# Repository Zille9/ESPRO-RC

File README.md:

# ESPRO-RC
Propeller-ESP32-Retro-Computer
- Der ESPRO-RC ist ein Minicomputer bestehend aus dem Parallax Propeller-IC (P8x32A) und einem ESP32 Dev-Kit als Grafik-Unit.
- Er kombiniert die einfache Programmierbarkeit und die Möglichkeit Programme von SD-Karte zu starten 
- mit den Grafikfähigkeiten der FabGl-Library im ESP32 als leistungsfähiges VGA-Terminal
- Als RAM wird ein PSRAM64H mit 8MByte Ram verwendet.
- Hauptprogramm ist ein umfangreicher Basic-Interpreter (weitere Programme sollen folgen)

Zur Installation werden benötigt:
- Arduino-IDE mit ESP32-Erweiterung
- FabGl-Library
- BST-Propeller-Compiler (im Ordner Software/P8X32A/BST)

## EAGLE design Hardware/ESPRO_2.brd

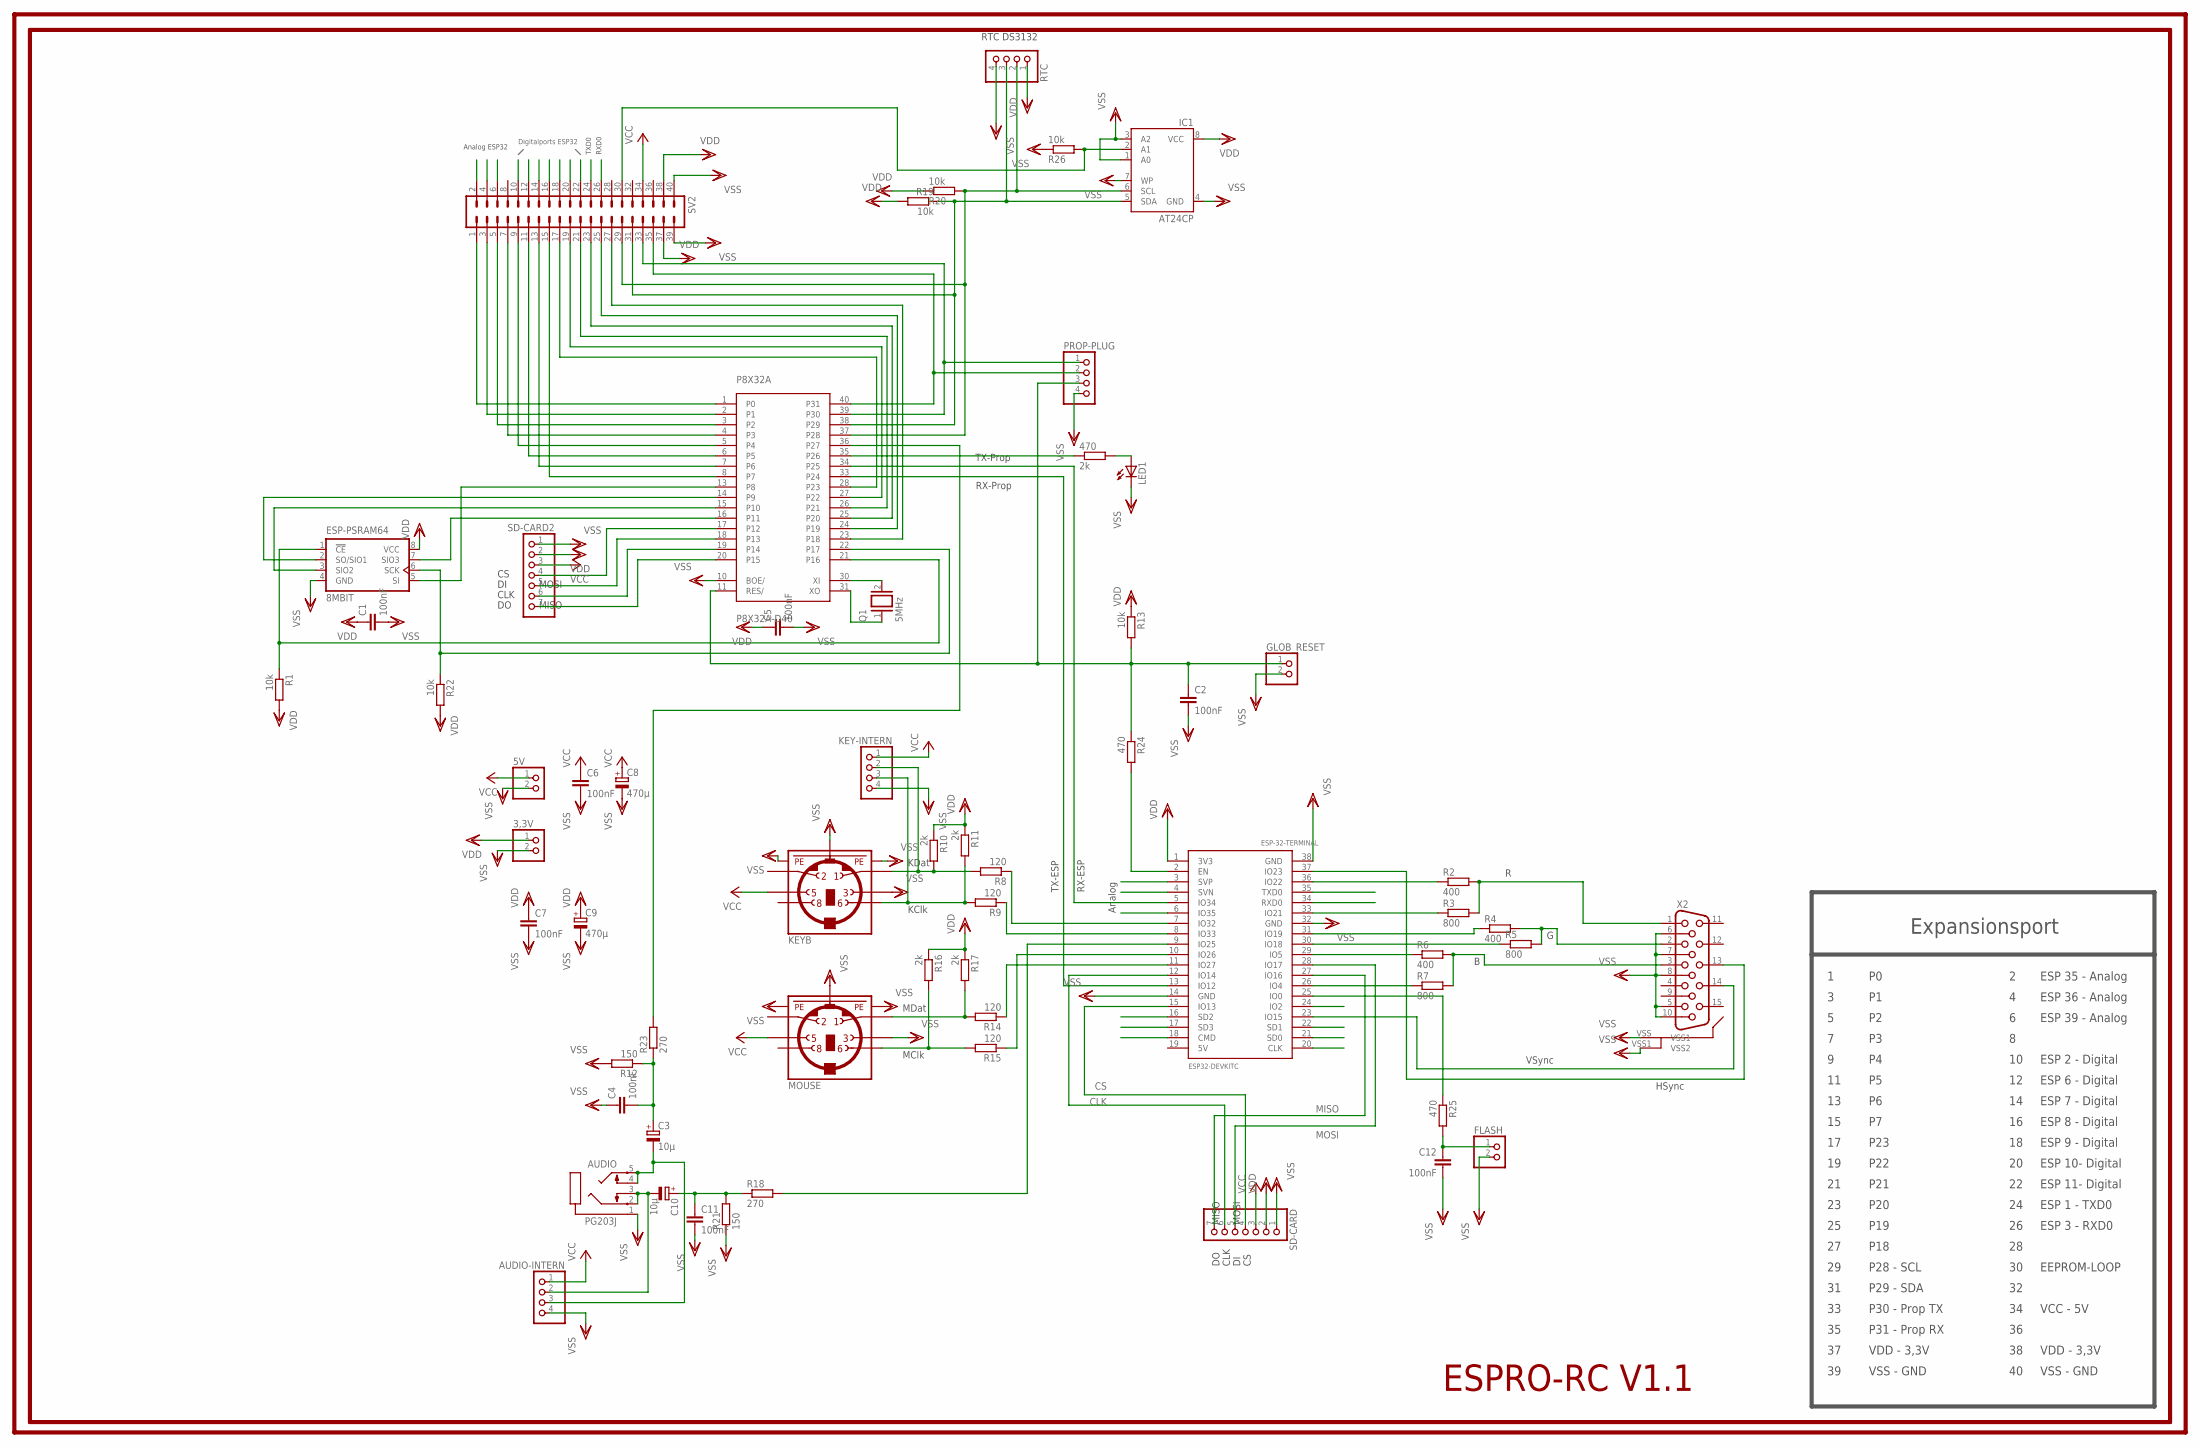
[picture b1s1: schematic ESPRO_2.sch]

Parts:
3,3V, 5V: PINHD-1X2; 1X02
470: 2k; 0204/7
AUDIO: PG203J
AUDIO-INTERN: PINHD-1X4; 1X04
C1, C2, C4, C5, C6, C7, C11, C12: 100nF; C025-030X050
C3, C10: 10µ; E2-4
C8, C9: 470µ; E3,5-10
ESP-32-TERMINAL: ESP32DEVKITC; ESP32-DEVKITC
ESP-PSRAM64: 8MBIT; DIL08
FLASH: PINHD-1X2; 1X02
GLOB_RESET: PINHD-1X2; 1X02
IC1: AT24CP; DIL08
KEY-INTERN: PINHD-1X4; 1X04
KEYB: MINI_DIN_6; M_DIN6
LED1: LED5MM
MOUSE: MINI_DIN_6; M_DIN6
P8X32A: P8X32A-D40
PROP-PLUG: PINHD-1X4; 1X04
Q1: 5MHz; QS
R1, R13, R19, R20, R22, R26: 10k; 0204/7
R2, R4, R6: 400; 0204/7
R3, R5, R7: 800; 0204/7
R8, R9, R14, R15: 120; 0204/7
R10, R11, R16, R17: 2k; 0204/7
R12, R21: 150; 0204/7
R18, R23: 270; 0204/7
R24, R25: 470; 0204/7
RTC: PINHD-1X4; 1X04
SD-CARD, SD-CARD2: PINHD-1X7; 1X07
SV2: ML40L
X2: HF15H; HDF15H

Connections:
A35: ESP-32-TERMINAL.6 (IO35), SV2.2
A36: ESP-32-TERMINAL.3 (SVP), SV2.4
A39: ESP-32-TERMINAL.4 (SVN), SV2.6
CLK: ESP-32-TERMINAL.12 (IO14), SD-CARD.6
CS: ESP-32-TERMINAL.15 (IO13), SD-CARD.4
E0: ESP-32-TERMINAL.25 (IO0), R25.1
E2: ESP-32-TERMINAL.5 (IO34), ESP-32-TERMINAL.24 (IO2), P8X32A.34 (P25), SV2.10
E6: ESP-32-TERMINAL.20 (CLK), SV2.12
E7: ESP-32-TERMINAL.21 (SD0), SV2.14
E8: ESP-32-TERMINAL.22 (SD1), SV2.16
E9: ESP-32-TERMINAL.16 (SD2), SV2.18
E10: ESP-32-TERMINAL.17 (SD3), SV2.20
E11: ESP-32-TERMINAL.18 (CMD), SV2.22
E12: ESP-32-TERMINAL.13 (IO12), P8X32A.33 (P24)
GND: P8X32A.9 (GND), P8X32A.29 (GND)
MISO: ESP-32-TERMINAL.27 (IO16), SD-CARD.7
MOSI: ESP-32-TERMINAL.28 (IO17), SD-CARD.5
unnamed: ESP-PSRAM64.1 (!CE!), P8X32A.21 (P16), R1.1
unnamed: ESP-PSRAM64.6 (SCK), P8X32A.22 (P17), R22.1
unnamed: P8X32A.20 (P15), SD-CARD2.7
unnamed: P8X32A.19 (P14), SD-CARD2.6
unnamed: P8X32A.18 (P13), SD-CARD2.5
unnamed: P8X32A.17 (P12), SD-CARD2.4
unnamed: 470.1, P8X32A.35 (P26)
unnamed: ESP-32-TERMINAL.9 (IO25), R18.2
unnamed: ESP-PSRAM64.5 (SI), P8X32A.13 (P8)
unnamed: ESP-PSRAM64.2 (SO/SIO1), P8X32A.14 (P9)
unnamed: ESP-PSRAM64.3 (SIO2), P8X32A.15 (P10)
unnamed: ESP-PSRAM64.7 (SIO3), P8X32A.16 (P11)
unnamed: C10.+, C11.1, R18.1, R21.2
unnamed: AUDIO.2, AUDIO.3, AUDIO-INTERN.2, C10.-
unnamed: ESP-32-TERMINAL.2 (EN), R24.2
unnamed: C12.1, FLASH.1, R25.2
unnamed: AUDIO.4, AUDIO.5, AUDIO-INTERN.3, C3.-
unnamed: C3.+, C4.2, R12.1, R23.1
unnamed: IC1.2 (A1), R26.2, SV2.30
unnamed: R6.2, R7.2, X2.3
unnamed: R4.2, R5.2, X2.2
unnamed: R2.2, R3.2, X2.1
unnamed: ESP-32-TERMINAL.36 (IO22), R2.1
unnamed: ESP-32-TERMINAL.33 (IO21), R3.1
unnamed: ESP-32-TERMINAL.31 (IO19), R4.1
unnamed: ESP-32-TERMINAL.30 (IO18), R5.1
unnamed: ESP-32-TERMINAL.29 (IO5), R6.1
unnamed: ESP-32-TERMINAL.26 (IO4), R7.1
unnamed: ESP-32-TERMINAL.37 (IO23), X2.13
unnamed: ESP-32-TERMINAL.23 (IO15), X2.14
unnamed: 470.2, LED1.A
unnamed: MOUSE.6, R15.2, R16.2
unnamed: MOUSE.1, R14.2, R17.2
unnamed: KEY-INTERN.2, KEYB.1, R8.2, R10.2
unnamed: ESP-32-TERMINAL.7 (IO32), R8.1
unnamed: KEY-INTERN.3, KEYB.6, R9.2, R11.2
unnamed: ESP-32-TERMINAL.8 (IO33), R9.1
unnamed: P8X32A.30 (XI), Q1.2
unnamed: ESP-32-TERMINAL.11 (IO27), R14.1
unnamed: ESP-32-TERMINAL.10 (IO26), R15.1
unnamed: P8X32A.31 (XO), Q1.1
P0: P8X32A.1 (P0), SV2.1
P1: P8X32A.2 (P1), SV2.3
P2: P8X32A.3 (P2), SV2.5
P3: P8X32A.4 (P3), SV2.7
P4: P8X32A.5 (P4), SV2.9
P5: P8X32A.6 (P5), SV2.11
P6: P8X32A.7 (P6), SV2.13
P7: P8X32A.8 (P7), SV2.15
P18: P8X32A.23 (P18), SV2.27
P19: P8X32A.24 (P19), SV2.25
P20: P8X32A.25 (P20), SV2.23
P21: P8X32A.26 (P21), SV2.21
P22: P8X32A.27 (P22), SV2.19
P23: P8X32A.28 (P23), SV2.17
P27: P8X32A.36 (P27), R23.2
P28: IC1.6 (SCL), P8X32A.37 (P28), R20.2, RTC.2, SV2.29
P29: IC1.5 (SDA), P8X32A.38 (P29), R19.1, RTC.3, SV2.31
P30: P8X32A.39 (P30), PROP-PLUG.1, SV2.33
P31: P8X32A.40 (P31), PROP-PLUG.2, SV2.35
RESET: C2.1, GLOB_RESET.1, P8X32A.11 (RES/), PROP-PLUG.3, R13.2, R24.1
RXD0: ESP-32-TERMINAL.34 (RXD0), SV2.26
TXD0: ESP-32-TERMINAL.35 (TXD0), SV2.24
VCC: 5V.1, AUDIO-INTERN.1, C6.1, C8.+, KEY-INTERN.1, KEYB.5, MOUSE.5, SD-CARD.3, SD-CARD2.3, SV2.34
VDD: 3,3V.1, C1.1, C5.1, C7.1, C9.+, ESP-32-TERMINAL.1 (3V3), ESP-PSRAM64.8 (VCC), IC1.8 (VCC), P8X32A.12 (VDD), P8X32A.32 (VDD), R1.2, R10.1, R11.1, R13.1, R16.1, R17.1, R19.2, R20.1, R22.2, RTC.1, SD-CARD.2, SD-CARD2.2, SV2.37, SV2.38
VSS: 3,3V.2, 5V.2, AUDIO.1, AUDIO-INTERN.4, C1.2, C2.2, C4.1, C5.2, C6.2, C7.2, C8.-, C9.-, C11.2, C12.2, ESP-32-TERMINAL.14 (GND), ESP-32-TERMINAL.32 (GND), ESP-32-TERMINAL.38 (GND), ESP-PSRAM64.4 (GND), FLASH.2, GLOB_RESET.2, IC1.1 (A0), IC1.3 (A2), IC1.4 (GND), IC1.7 (WP), KEY-INTERN.4, KEYB.3, KEYB.SH1 (PE1), KEYB.SH2 (PE2), KEYB.SH3 (PE3), LED1.K (C), MOUSE.3, MOUSE.SH1 (PE1), MOUSE.SH2 (PE2), MOUSE.SH3 (PE3), P8X32A.10 (BOE/), PROP-PLUG.4, R12.2, R21.1, R26.1, RTC.4, SD-CARD.1, SD-CARD2.1, SV2.39, SV2.40, X2.5, X2.6, X2.7, X2.8, X2.10, X2.VSS (VSS1), X2.VSS1 (VSS2)

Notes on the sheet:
CLK
MISO
MOSI
MDat
MClk
KDat
KClk
VSync
HSync
RTC DS3132
Analog
Analog ESP32
Digitalports ESP32
RX-Prop
TX-Prop
TX-ESP
RX-ESP
TXD0
RXD0
Expansionsport
P19
P18
P20
P21
P22
P23
P28 - SCL
P29 - SDA
P30 - Prop TX
P31 - Prop RX
VDD - 3,3V
VSS - GND
VCC - 5V
ESP 35 - Analog
ESP 36 - Analog
ESP 39 - Analog
ESP 2 - Digital
ESP 6 - Digital
ESP 7 - Digital
ESP 8 - Digital

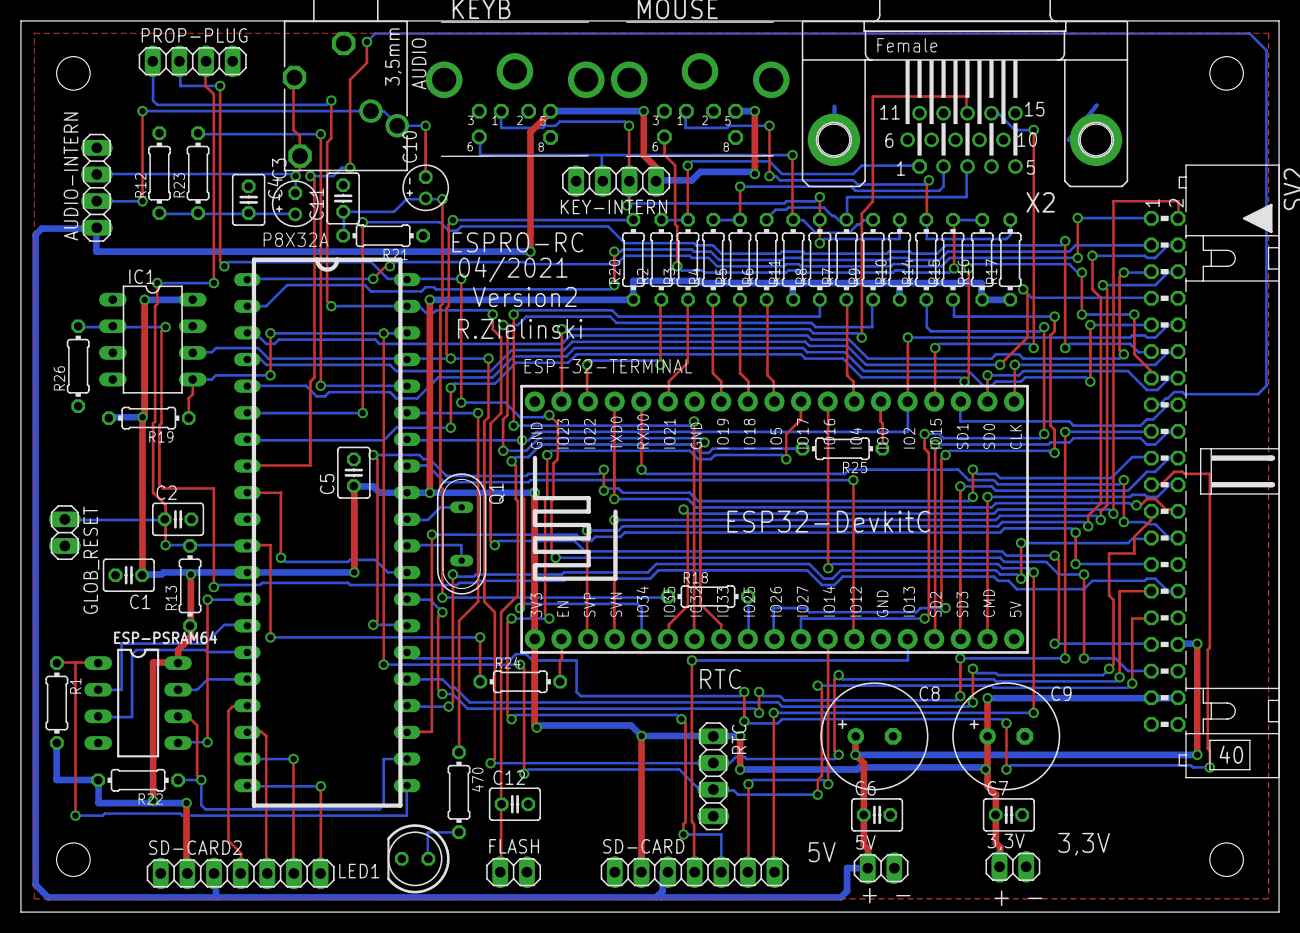
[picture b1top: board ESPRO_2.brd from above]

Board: 2 copper layers, 120.0 x 85.0 mm, 60 parts (0 on the bottom side), 83 nets.

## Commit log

2021-04-01 Start
2021-04-01 Ressourcen
2021-04-03 Hardware
2021-04-04 Update Hardware
2021-04-09 Software-Ordner
2021-04-09 Reorganisation
2021-04-09 Fehler in REM-Befehl
2021-04-09 Revision
2021-04-09 Hardware Update

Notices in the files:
parts and their libraries:
ESP-PSRAM: Copyright (C) 2008, Bob Starr
